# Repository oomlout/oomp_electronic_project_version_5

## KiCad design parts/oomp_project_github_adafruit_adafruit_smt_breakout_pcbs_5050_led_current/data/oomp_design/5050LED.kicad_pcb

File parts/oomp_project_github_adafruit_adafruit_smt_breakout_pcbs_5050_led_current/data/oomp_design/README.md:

# OOMP KiCad design copy

Open `5050LED.kicad_pro` (or the `.kicad_pcb` / `.kicad_sch`) in KiCad. Local OOMP libraries are under `libraries/`. Original inputs are preserved in [../original/](../original/).

Only verified unchanged installed KiCad defaults were renamed. Modified, custom, unmatched and unavailable items remain unchanged. Soldering variants are never swapped during conversion. Existing pad coordinates, nets and UUIDs are preserved.

See [conversion_report.yaml](conversion_report.yaml) for every conversion and skip. Copy this directory before editing; regeneration refuses to overwrite edited design files.

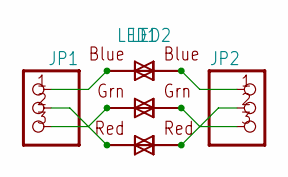
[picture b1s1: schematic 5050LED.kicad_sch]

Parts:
JP1, JP2: PINHD-1X3CB; 1X03-CLEANBIG
LED1, LED2: RGBLED5050

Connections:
unnamed: JP1.1, LED1.3 (BLUE_A), LED2.4 (BLUE_C)
unnamed: JP1.2, LED1.2 (RED_A), LED2.5 (RED_C)
unnamed: JP1.3, LED1.1 (GREEN_A), LED2.6 (GREEN_C)
unnamed: JP2.1, LED1.4 (BLUE_C), LED2.3 (BLUE_A)
unnamed: JP2.2, LED1.5 (RED_C), LED2.2 (RED_A)
unnamed: JP2.3, LED1.6 (GREEN_C), LED2.1 (GREEN_A)

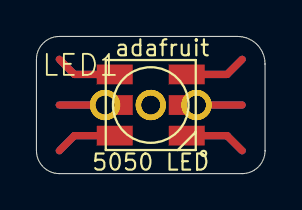
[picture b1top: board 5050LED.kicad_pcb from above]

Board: 2 copper layers, 12.7 x 7.6 mm, 4 parts (1 on the bottom side), 6 nets.

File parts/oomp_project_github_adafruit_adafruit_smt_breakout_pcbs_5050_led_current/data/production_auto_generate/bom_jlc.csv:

Comment,Designator,Footprint,LCSC Part #
,"JP1,JP2",5050LED-import-fps:1X03-CLEANBIG,C49257
RGBLED5050,"LED1,LED2",5050LED-import-fps:RGBLED5050,

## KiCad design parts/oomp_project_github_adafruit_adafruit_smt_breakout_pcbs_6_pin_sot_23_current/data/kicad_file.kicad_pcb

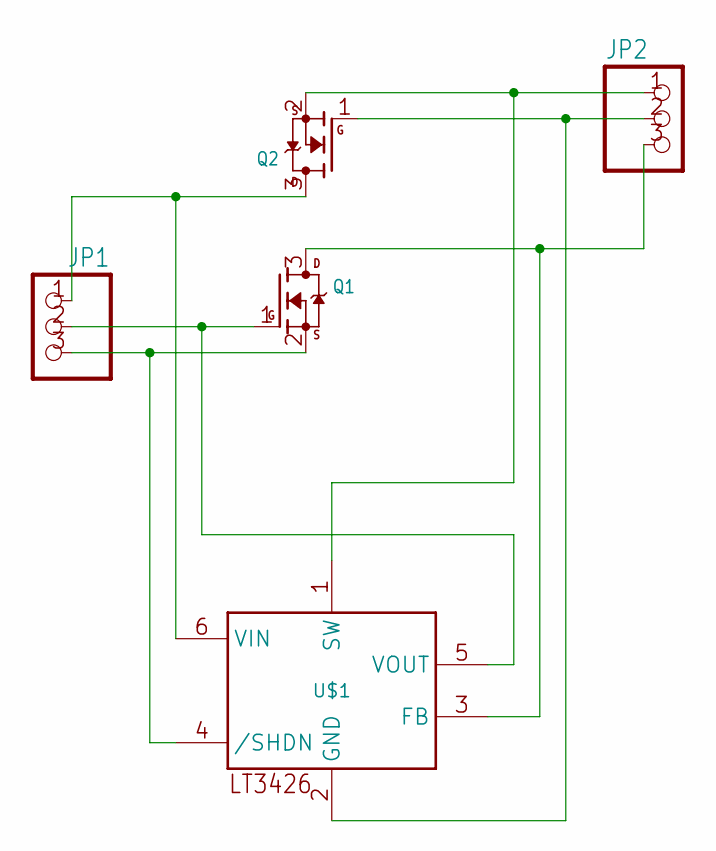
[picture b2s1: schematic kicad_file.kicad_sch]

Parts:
JP1, JP2: PINHD-1X3CB; 1X03-CLEANBIG
Q1, Q2: MOSFET-NREFLOW; SOT23
U$1: LT3426; SOT23-6

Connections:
GND: JP2.2, Q2.1 (G), U$1.2 (GND)
unnamed: JP2.3, Q1.3 (D), U$1.3 (FB)
unnamed: JP1.2, Q1.1 (G), U$1.5 (VOUT)
unnamed: JP1.3, Q1.2 (S), U$1.4 (/SHDN)
unnamed: JP2.1, Q2.2 (S), U$1.1 (SW)
unnamed: JP1.1, Q2.3 (D), U$1.6 (VIN)

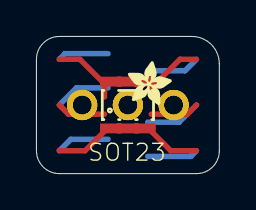
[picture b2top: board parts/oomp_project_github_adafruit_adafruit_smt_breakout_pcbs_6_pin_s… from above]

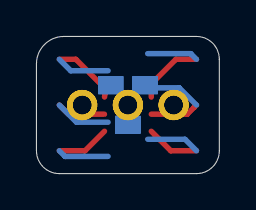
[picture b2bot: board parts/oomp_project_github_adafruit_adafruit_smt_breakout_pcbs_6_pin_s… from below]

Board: 2 copper layers, 10.2 x 7.6 mm, 6 parts (2 on the bottom side), 6 nets.

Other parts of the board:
U$2: ADAFRUIT_2.5MM

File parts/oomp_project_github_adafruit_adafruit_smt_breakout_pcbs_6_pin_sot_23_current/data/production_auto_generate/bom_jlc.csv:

Comment,Designator,Footprint,LCSC Part #
,"JP1,JP2",6-pin SOT-23-import-fps:1X03-CLEANBIG,C49257
,U$2,6-pin SOT-23-import-fps:ADAFRUIT_2.5MM,
,"Q1,Q2",6-pin SOT-23-import-fps:SOT23,
LT3426,U$1,6-pin SOT-23-import-fps:SOT23-6,

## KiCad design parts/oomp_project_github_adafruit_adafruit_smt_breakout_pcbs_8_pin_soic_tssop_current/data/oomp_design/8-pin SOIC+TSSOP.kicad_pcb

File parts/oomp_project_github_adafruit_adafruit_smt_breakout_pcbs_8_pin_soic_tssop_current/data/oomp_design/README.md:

# OOMP KiCad design copy

Open `8-pin SOIC+TSSOP.kicad_pro` (or the `.kicad_pcb` / `.kicad_sch`) in KiCad. Local OOMP libraries are under `libraries/`. Original inputs are preserved in [../original/](../original/).

Only verified unchanged installed KiCad defaults were renamed. Modified, custom, unmatched and unavailable items remain unchanged. Soldering variants are never swapped during conversion. Existing pad coordinates, nets and UUIDs are preserved.

See [conversion_report.yaml](conversion_report.yaml) for every conversion and skip. Copy this directory before editing; regeneration refuses to overwrite edited design files.

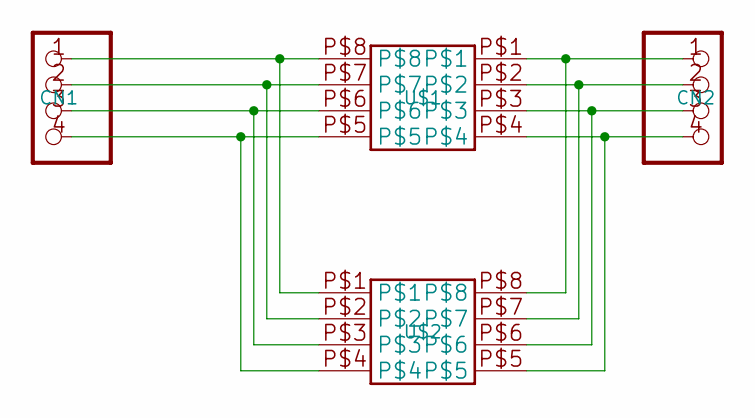
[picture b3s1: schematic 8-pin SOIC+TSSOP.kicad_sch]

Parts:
CN1, CN2: PADS-4
U$1: 8-PINSOIC-NW; SO8NW
U$2: 8-PINTSSOP; TSSOP8

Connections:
unnamed: CN1.1, U$1.P$8, U$2.P$1
unnamed: CN2.1, U$1.P$1, U$2.P$8
unnamed: CN2.2, U$1.P$2, U$2.P$7
unnamed: CN2.3, U$1.P$3, U$2.P$6
unnamed: CN2.4, U$1.P$4, U$2.P$5
unnamed: CN1.2, U$1.P$7, U$2.P$2
unnamed: CN1.3, U$1.P$6, U$2.P$3
unnamed: CN1.4, U$1.P$5, U$2.P$4

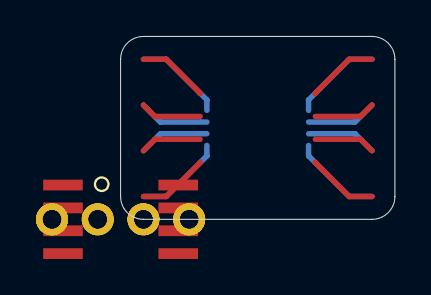
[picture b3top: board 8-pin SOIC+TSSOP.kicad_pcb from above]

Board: 2 copper layers, 15.2 x 10.2 mm, 4 parts (1 on the bottom side), 8 nets.

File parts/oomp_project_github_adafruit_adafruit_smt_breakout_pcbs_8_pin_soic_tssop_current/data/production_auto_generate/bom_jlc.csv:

Comment,Designator,Footprint,LCSC Part #
,"CN1,CN2",8-pin SOIC+TSSOP-import-fps:PADS-4,
8-PINSOIC-NW,U$1,8-pin SOIC+TSSOP-import-fps:SO8NW,
8-PINTSSOP,U$2,8-pin SOIC+TSSOP-import-fps:TSSOP8,

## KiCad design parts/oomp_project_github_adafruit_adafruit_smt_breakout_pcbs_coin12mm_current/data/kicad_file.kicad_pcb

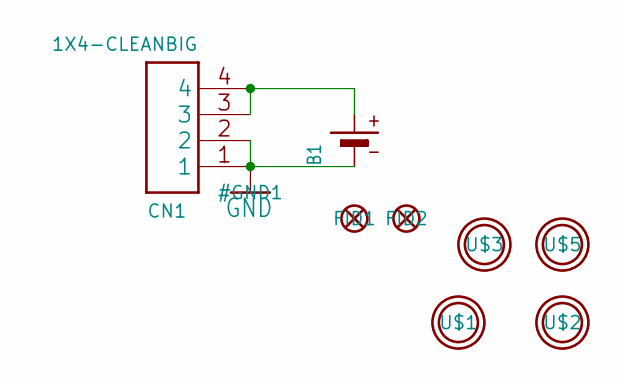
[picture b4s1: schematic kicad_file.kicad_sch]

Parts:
B1: BATTERYCR1220_SMT; CR1220
CN1: 1X4-CLEANBIG; 1X04-CLEANBIG
FID1, FID2: FIDUCIAL""; FIDUCIAL_1MM
U$1, U$2, U$3, U$5: MOUNTINGHOLE2.5; MOUNTINGHOLE_2.5_PLATED

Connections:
GND: B1.-, CN1.1, CN1.2
unnamed: B1.+$1 (+), CN1.3, CN1.4

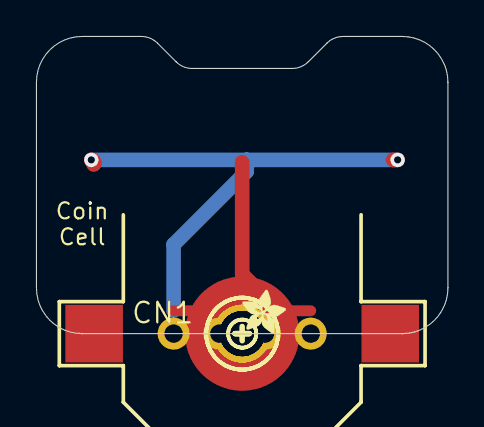
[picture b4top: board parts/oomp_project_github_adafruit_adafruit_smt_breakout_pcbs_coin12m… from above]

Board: 2 copper layers, 22.9 x 16.5 mm, 12 parts (1 on the bottom side), 2 nets.

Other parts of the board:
U$4: ADAFRUIT_5MM
U$6: SYMBOL_PLUS
U$7: SYMBOL_MINUS
U$8: ADAFRUIT_2.5MM
